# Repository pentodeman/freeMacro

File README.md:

# freeMacro rev. 1
A simple macro keypad that invokes key combinations, prints strings of text, and types special characters.

Special thanks to Arduino LLC for providing the Keyboard library that was used to create this project.
The library is available under:
https://github.com/arduino-libraries/Keyboard

## Features
* Typing strings, invoking macros, and typing special characters from the Unicode table
* 13 assignable banks with combinations of all three types of keypresses
* On the fly assignment of target operating system (Linux, Windows, macOS)
* Dependency free, plug and play
* Config generation handled by genConfig

## Default Firmware Behavior
* On power on, the board will flash each LED individually from the F key to the 0 key.
* Idle backlight should be steady without any flickering.
* On each keypress, only that key will be lit. Others will not.
* Holding down any key from 0 to C changes the current bank to that of they key held down.
* Pressing a key will invoke its macro (key combo, string, or Unicode).
* Holding down keys from D to F will change the target operating system:
  * D: Linux
  * E: Windows
  * F: macOS
* The default config initializes the bank to 9 and OS to Linux, if you prefer to use another combination, edit "banks.layout" and run genConfig (more instructions later).
* Bank and OS changes are indicated by the flash pattern:
  * fast: bank change
  * slow: OS change

## Modifying the config
* The firmware consists of two files:
  * freeMacro-firmware.ino: main firmware file that handles the logic
  * config.h: header file that houses all the functions called on keystrokes -> this is the config file
* Option 1: you can edit config.h directly if you want more control over your device (make sure to back up the default config in case of a rollback).
* Option 2: use genConfig and edit the soft config file (banks.layout).

## Arduino IDE is required for uploading the firmware (or Arduino CLI)
* Pro Micro boards are usually miniaturized Arduino Leonardos, selecting Arduino Leonardo in your board manager will likely work.
* In case of upload issues, make sure you selected the correct board and plugged it in. Communication issues can be caused by the serial port being busy or not having permissions to use the port (Googling the programmer error will usually solve the issue).

## Using genConfig
* This repo provides the source code for genConfig and a Linux binary.
* This program was only tested on Linux. Windows or macOS users may need to make changes to the source code, but this is unlikely. If you're using one of these systems, try compiling it first. For this you will need a C++ compiler. I used g++.
* Compiling genConfig from source:
  * This program does not use any third-party dependencies.
  * The only requirement for compilation is the C++ compiler itself; g++ is recommended.
  * To compile the program, follow these steps:
  
    ```git clone https://github.com/pentodeman/freeMacro```
    
    ```cd freeMacro```

    ```g++ genConfig.cpp -o genConfig```

    ```./genConfig --help```
  * It is not recommended to add genConfig to any binary directories (/bin, /sbin, /usr/bin, /usr/sbin, etc...) as the program outputs the file to its current working directory.
  * genConfig will look for the file called banks.layout in its current working directory and will output config.h
  * To generate a new config simply run:

    ```./genConfig``` for silent generation

    or

    ```./genConfig -v``` or ```./genConfig --verbose``` for verbose generation.
  * To use the new config, move the new config.h to the "freeMacro-firmware" directory and replace the old one (backing up your configs is recommended).
  * Once the new config.h is placed in the firmware directory, open the .ino file in Arduino IDE and upload it to your freeMacro board.
  * Instructions for modifying banks.layout are in the file itself and include a general template with all possible keywords.

## Assembly
* Required materials:
  * 1 PCB **make sure the PCB thickness is 1.6 mm** (Gerber files attached)
  * 16 3-pin full size mechanical switches of any kind (5-pin update coming soon in revision 2)
  * Electronic components listed in the BOM
  * 3D printed case (.stl files attached; feel free to design your own (.step file of the PCB can be generated in KiCad))
  * Low profile keycaps (currently full size keycaps have clearance issues with the enclosure)
* Tips for soldering the PCB:
  1. Start with the smallest and most repetitive components first (all passive and discrete components on the top plane).
  2. Solder the two multiplexer ICs.
  3. Clean the PCB thoroughly with isopropanol.
  4. Then solder the bottom LED current limiting resistors and clean the board again.
  5. Solder the Arduino Pro Micro FLUSH with the PCB. The case is designed to fit the microcontroller soldered directly to the PCB using included headers (see images folder).
    * feed the headers from the bottom of the freeMacro PCB and place the Arduino on top.
  6. After all electronic components are soldered, test the board by bridging switch pads with tweezers or any other conductor. Open any text editor and check if all characters are printed. Bank 9 of the default config is a good test.
  7. Once everything works, solder the switches. If you use the top shell with the plate, print the plate first and populate it with switches. It works as a good soldering guide. Make sure to test fit the entire device before soldering the switches.
  8. After soldering the switches, feed the LEDs throughand solder them. It's a good idea to just feed them and bend the leads for testing. Do it and plug in the board. If you see all LEDs shining (with some wiggling due to the lack of solder), the board works.
  9. Trim the leads, clean the board one last time, and assemble the case.
  10. Your board is ready, it's a good time to double check everything.

### Please note that this project is not a polished product. It's meant to be a fun project to tinker and experiment with. Working on it took me a total of one week worth of deisgn, coding, assembly, and testing. Please take imperfections with a grain of salt, as this is only a project delivered by a nerd to his fellow nerds. Happy tinkering!

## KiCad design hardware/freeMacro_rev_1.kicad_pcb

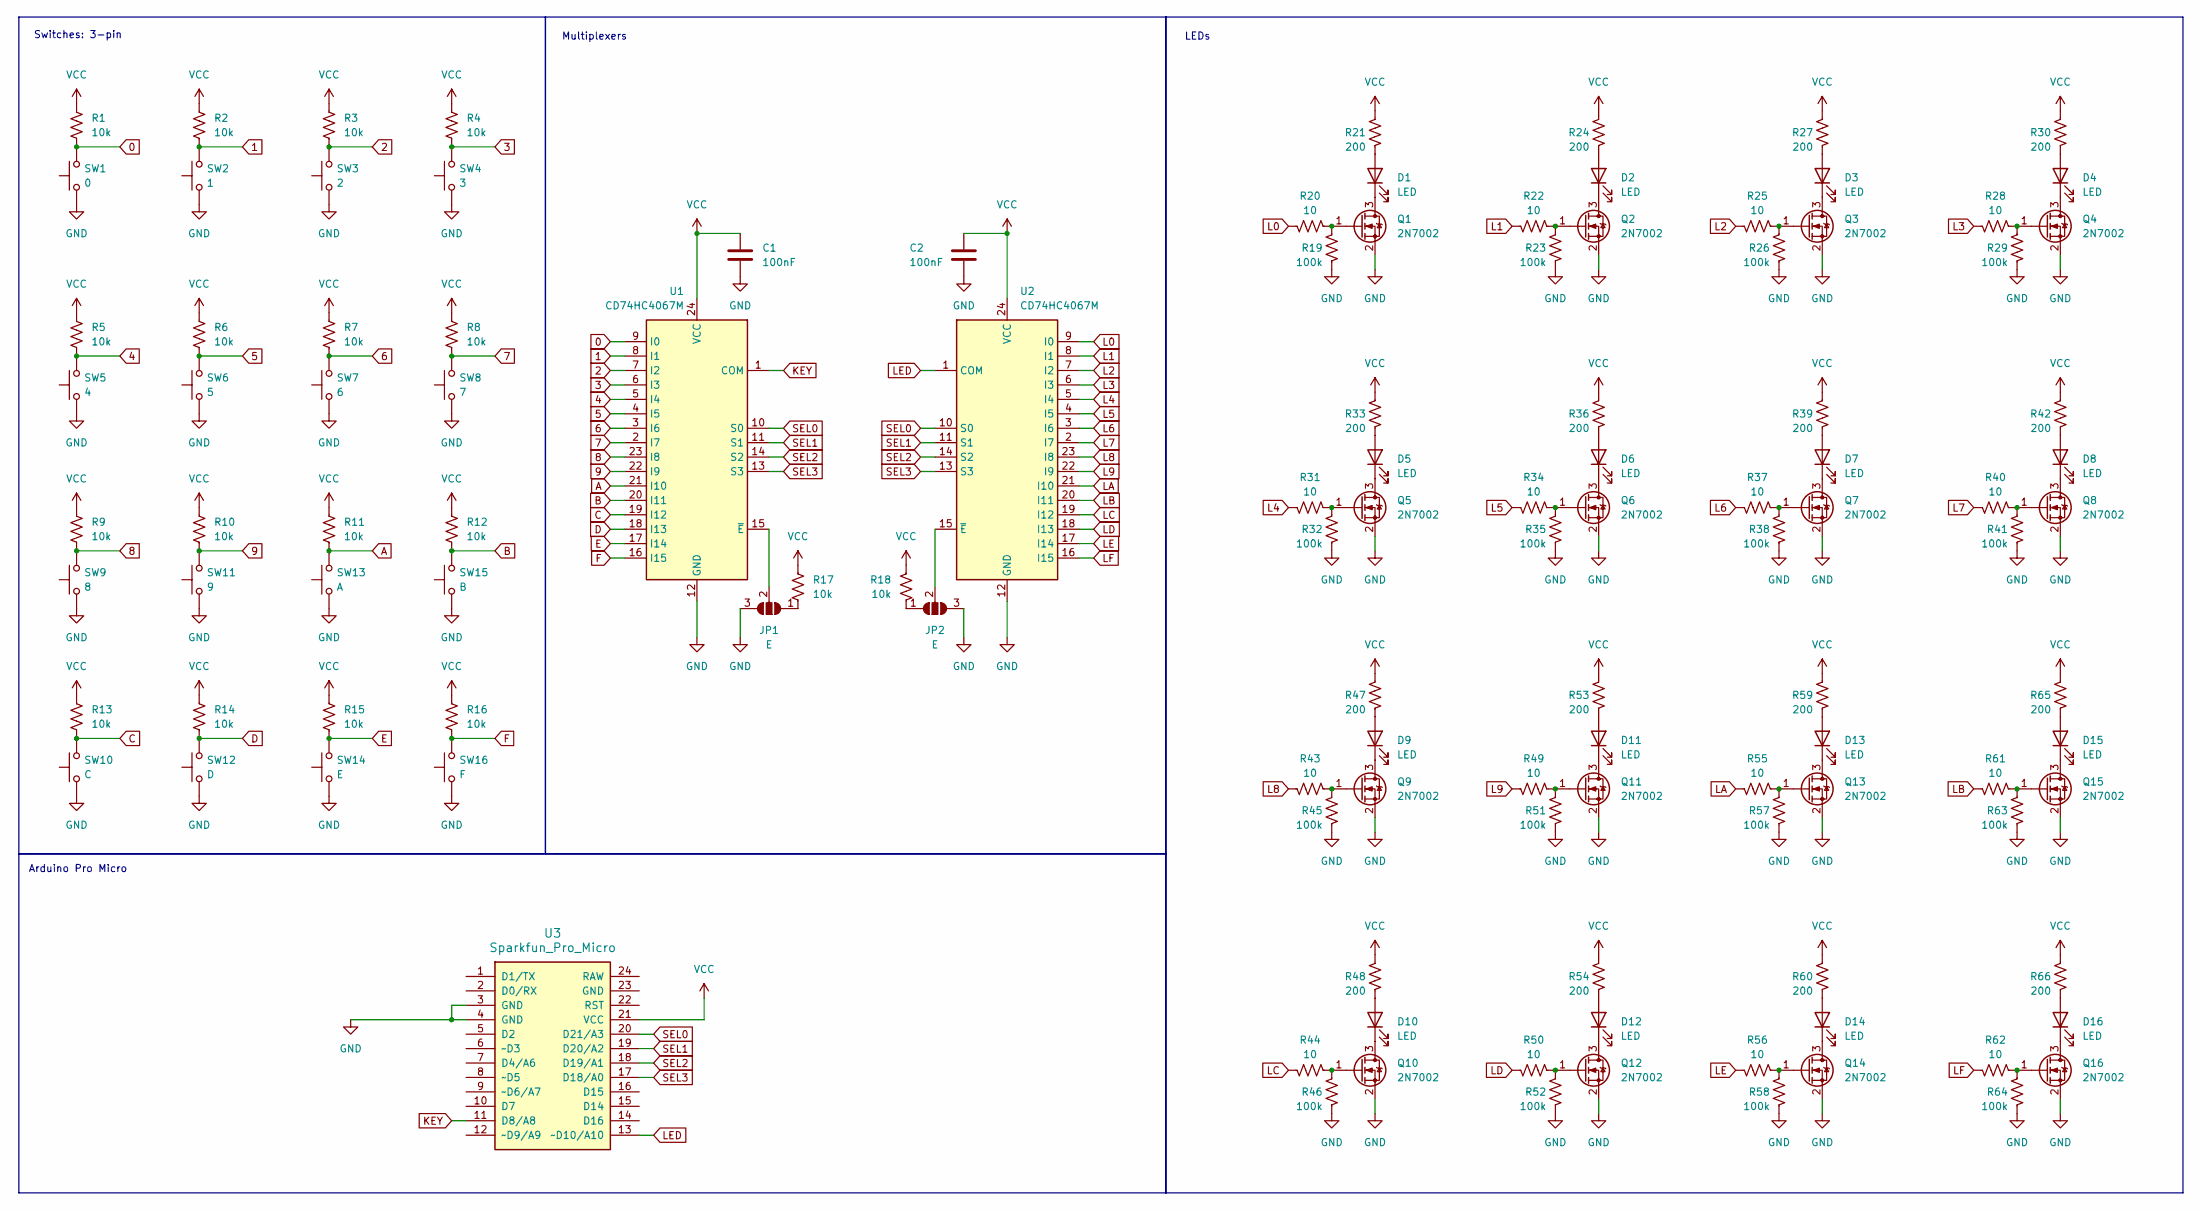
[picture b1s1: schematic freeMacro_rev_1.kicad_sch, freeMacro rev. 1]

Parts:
C1, C2: 100nF; C_0603_1608Metric_Pad1.08x0.95mm_HandSolder
D1, D2, D3, D4, D5, D6, D7, D8, D9, D10, D11, D12, D13, D14, D15, D16: LED; LED_D3.0mm
JP1, JP2: E; SolderJumper-3_P2.0mm_Open_TrianglePad1.0x1.5mm
Q1, Q2, Q3, Q4, Q5, Q6, Q7, Q8, Q9, Q10, Q11, Q12, Q13, Q14, Q15, Q16: 2N7002; SOT-23
R1, R2, R3, R4, R5, R6, R7, R8, R9, R10, R11, R12, R13, R14, R15, R16, R17, R18: 10k; R_0603_1608Metric_Pad0.98x0.95mm_HandSolder
R19, R23, R26, R29, R32, R35, R38, R41, R45, R46, R51, R52, R57, R58, R63, R64: 100k; R_0603_1608Metric_Pad0.98x0.95mm_HandSolder
R20, R22, R25, R28, R31, R34, R37, R40, R43, R44, R49, R50, R55, R56, R61, R62: 10; R_0603_1608Metric_Pad0.98x0.95mm_HandSolder
R21, R24, R27, R30, R33, R36, R39, R42, R47, R48, R53, R54, R59, R60, R65, R66: 200; R_0603_1608Metric_Pad0.98x0.95mm_HandSolder
SW1: 0; SW_Cherry_MX_1.00u_Plate
SW2: 1; SW_Cherry_MX_1.00u_Plate
SW3: 2; SW_Cherry_MX_1.00u_Plate
SW4: 3; SW_Cherry_MX_1.00u_Plate
SW5: 4; SW_Cherry_MX_1.00u_Plate
SW6: 5; SW_Cherry_MX_1.00u_Plate
SW7: 6; SW_Cherry_MX_1.00u_Plate
SW8: 7; SW_Cherry_MX_1.00u_Plate
SW9: 8; SW_Cherry_MX_1.00u_Plate
SW10: C; SW_Cherry_MX_1.00u_Plate
SW11: 9; SW_Cherry_MX_1.00u_Plate
SW12: D; SW_Cherry_MX_1.00u_Plate
SW13: A; SW_Cherry_MX_1.00u_Plate
SW14: E; SW_Cherry_MX_1.00u_Plate
SW15: B; SW_Cherry_MX_1.00u_Plate
SW16: F; SW_Cherry_MX_1.00u_Plate
U1, U2: CD74HC4067M; SOIC-24W_7.5x15.4mm_P1.27mm
U3: Sparkfun_Pro_Micro

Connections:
0: R1.2, SW1.2, U1.9 (I0)
1: R2.2, SW2.2, U1.8 (I1)
2: R3.2, SW3.2, U1.7 (I2)
3: R4.2, SW4.2, U1.6 (I3)
4: R5.2, SW5.2, U1.5 (I4)
5: R6.2, SW6.2, U1.4 (I5)
6: R7.2, SW7.2, U1.3 (I6)
7: R8.2, SW8.2, U1.2 (I7)
8: R9.2, SW9.2, U1.23 (I8)
9: R10.2, SW11.2, U1.22 (I9)
A: R11.2, SW13.2, U1.21 (I10)
B: R12.2, SW15.2, U1.20 (I11)
C: R13.2, SW10.2, U1.19 (I12)
D: R14.2, SW12.2, U1.18 (I13)
E: R15.2, SW14.2, U1.17 (I14)
F: R16.2, SW16.2, U1.16 (I15)
GND: C1.2, C2.2, JP1.3 (B), JP2.3 (B), Q1.2 (S), Q2.2 (S), Q3.2 (S), Q4.2 (S), Q5.2 (S), Q6.2 (S), Q7.2 (S), Q8.2 (S), Q9.2 (S), Q10.2 (S), Q11.2 (S), Q12.2 (S), Q13.2 (S), Q14.2 (S), Q15.2 (S), Q16.2 (S), R19.2, R23.2, R26.2, R29.2, R32.2, R35.2, R38.2, R41.2, R45.2, R46.2, R51.2, R52.2, R57.2, R58.2, R63.2, R64.2, SW1.1, SW2.1, SW3.1, SW4.1, SW5.1, SW6.1, SW7.1, SW8.1, SW9.1, SW10.1, SW11.1, SW12.1, SW13.1, SW14.1, SW15.1, SW16.1, U1.12 (GND), U2.12 (GND), U3.3 (GND), U3.4 (GND)
KEY: U1.1 (COM), U3.11 (D8/A8)
L0: R20.1, U2.9 (I0)
L1: R22.1, U2.8 (I1)
L2: R25.1, U2.7 (I2)
L3: R28.1, U2.6 (I3)
L4: R31.1, U2.5 (I4)
L5: R34.1, U2.4 (I5)
L6: R37.1, U2.3 (I6)
L7: R40.1, U2.2 (I7)
L8: R43.1, U2.23 (I8)
L9: R49.1, U2.22 (I9)
LA: R55.1, U2.21 (I10)
LB: R61.1, U2.20 (I11)
LC: R44.1, U2.19 (I12)
LD: R50.1, U2.18 (I13)
LE: R56.1, U2.17 (I14)
LED: U2.1 (COM), U3.13 (~D10/A10)
LF: R62.1, U2.16 (I15)
unnamed: D1.2 (A), R21.2
unnamed: D1.1 (K), Q1.3 (D)
unnamed: D2.2 (A), R24.2
unnamed: D2.1 (K), Q2.3 (D)
unnamed: D3.2 (A), R27.2
unnamed: D3.1 (K), Q3.3 (D)
unnamed: D4.2 (A), R30.2
unnamed: D4.1 (K), Q4.3 (D)
unnamed: D5.2 (A), R33.2
unnamed: D5.1 (K), Q5.3 (D)
unnamed: D6.2 (A), R36.2
unnamed: D6.1 (K), Q6.3 (D)
unnamed: D7.2 (A), R39.2
unnamed: D7.1 (K), Q7.3 (D)
unnamed: D8.2 (A), R42.2
unnamed: D8.1 (K), Q8.3 (D)
unnamed: D9.2 (A), R47.2
unnamed: D9.1 (K), Q9.3 (D)
unnamed: D10.2 (A), R48.2
unnamed: D10.1 (K), Q10.3 (D)
unnamed: D11.2 (A), R53.2
unnamed: D11.1 (K), Q11.3 (D)
unnamed: D12.2 (A), R54.2
unnamed: D12.1 (K), Q12.3 (D)
unnamed: D13.2 (A), R59.2
unnamed: D13.1 (K), Q13.3 (D)
unnamed: D14.2 (A), R60.2
unnamed: D14.1 (K), Q14.3 (D)
unnamed: D15.2 (A), R65.2
unnamed: D15.1 (K), Q15.3 (D)
unnamed: D16.2 (A), R66.2
unnamed: D16.1 (K), Q16.3 (D)
unnamed: JP1.1 (A), R17.2
unnamed: JP1.2 (C), U1.15 (~E)
unnamed: JP2.1 (A), R18.2
unnamed: JP2.2 (C), U2.15 (~E)
unnamed: Q1.1 (G), R19.1, R20.2
unnamed: Q2.1 (G), R22.2, R23.1
unnamed: Q3.1 (G), R25.2, R26.1
unnamed: Q4.1 (G), R28.2, R29.1
unnamed: Q5.1 (G), R31.2, R32.1
unnamed: Q6.1 (G), R34.2, R35.1
unnamed: Q7.1 (G), R37.2, R38.1
unnamed: Q8.1 (G), R40.2, R41.1
unnamed: Q9.1 (G), R43.2, R45.1
unnamed: Q10.1 (G), R44.2, R46.1
unnamed: Q11.1 (G), R49.2, R51.1
unnamed: Q12.1 (G), R50.2, R52.1
unnamed: Q13.1 (G), R55.2, R57.1
unnamed: Q14.1 (G), R56.2, R58.1
unnamed: Q15.1 (G), R61.2, R63.1
unnamed: Q16.1 (G), R62.2, R64.1
SEL0: U1.10 (S0), U2.10 (S0), U3.20 (D21/A3)
SEL1: U1.11 (S1), U2.11 (S1), U3.19 (D20/A2)
SEL2: U1.14 (S2), U2.14 (S2), U3.18 (D19/A1)
SEL3: U1.13 (S3), U2.13 (S3), U3.17 (D18/A0)
VCC: C1.1, C2.1, R1.1, R2.1, R3.1, R4.1, R5.1, R6.1, R7.1, R8.1, R9.1, R10.1, R11.1, R12.1, R13.1, R14.1, R15.1, R16.1, R17.1, R18.1, R21.1, R24.1, R27.1, R30.1, R33.1, R36.1, R39.1, R42.1, R47.1, R48.1, R53.1, R54.1, R59.1, R60.1, R65.1, R66.1, U1.24 (VCC), U2.24 (VCC), U3.21 (VCC)

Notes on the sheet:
Multiplexers
Switches: 3-pin
LEDs
Arduino Pro Micro

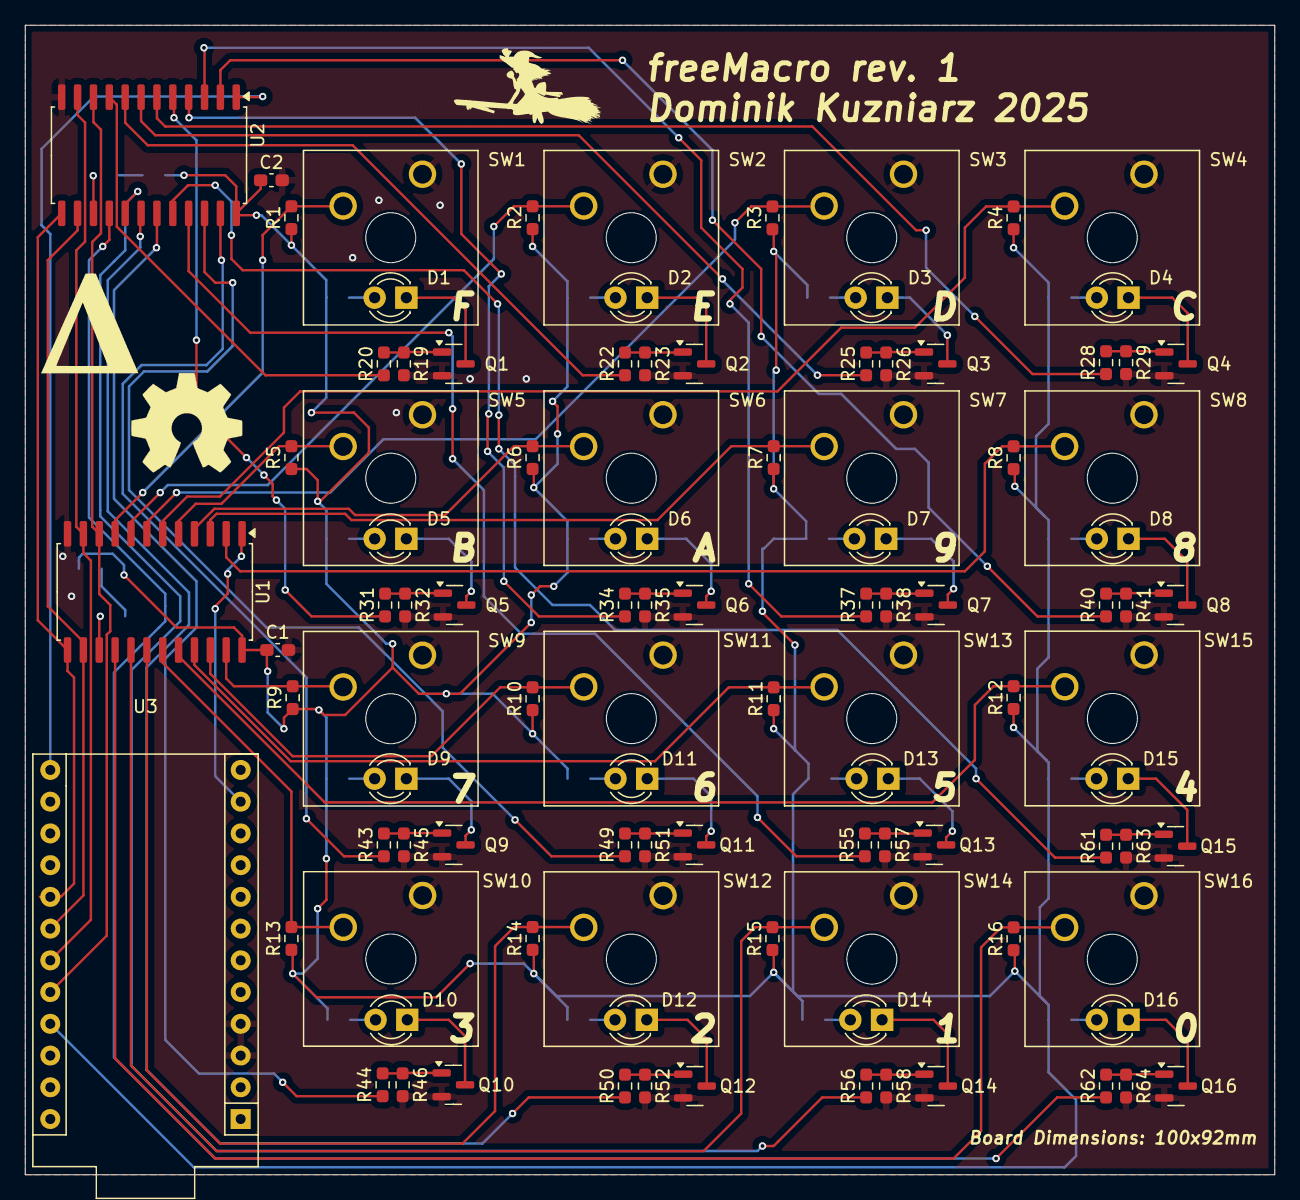
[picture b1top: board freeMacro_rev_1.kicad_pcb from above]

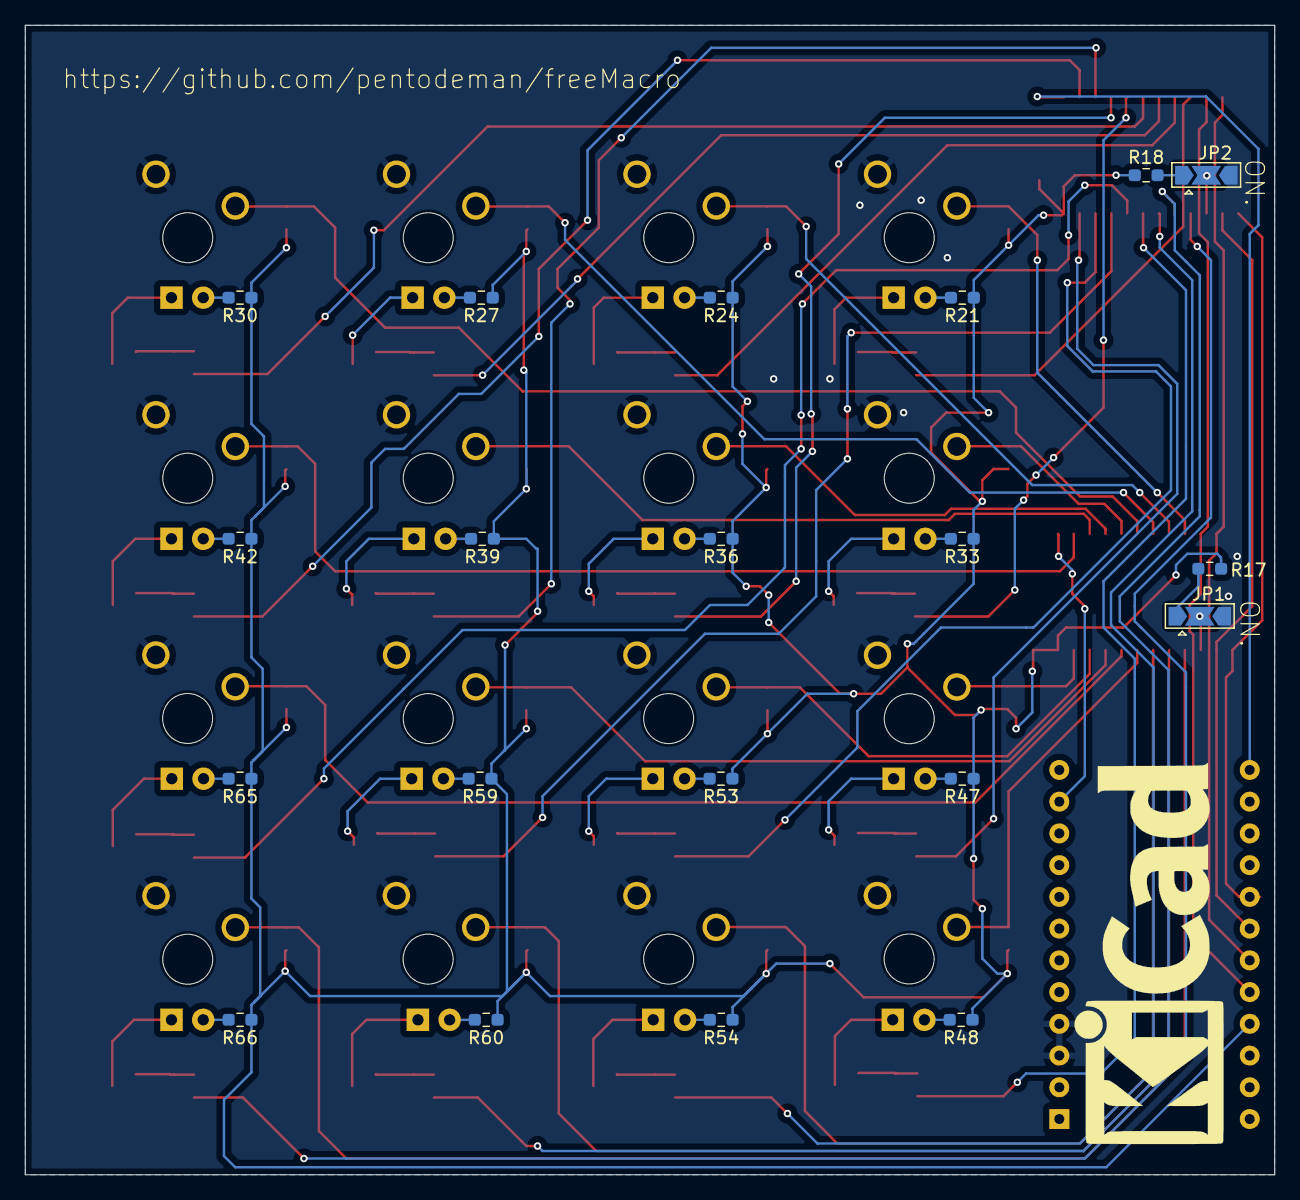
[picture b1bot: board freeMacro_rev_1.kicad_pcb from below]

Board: 2 copper layers, 100.0 x 92.0 mm, 121 parts (20 on the bottom side), 92 nets.

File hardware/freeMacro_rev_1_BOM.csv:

"Reference","Value","Datasheet","Footprint","Qty","DNP"
"C1,C2","100nF","~","Capacitor_SMD:C_0603_1608Metric_Pad1.08x0.95mm_HandSolder","2",""
"D1,D2,D3,D4,D5,D6,D7,D8,D9,D10,D11,D12,D13,D14,D15,D16","LED","~","LED_THT:LED_D3.0mm","16",""
"Q1,Q2,Q3,Q4,Q5,Q6,Q7,Q8,Q9,Q10,Q11,Q12,Q13,Q14,Q15,Q16","2N7002","https://www.onsemi.com/pub/Collateral/NDS7002A-D.PDF","Package_TO_SOT_SMD:SOT-23","16",""
"R1,R2,R3,R4,R5,R6,R7,R8,R9,R10,R11,R12,R13,R14,R15,R16,R17,R18","10k","~","Resistor_SMD:R_0603_1608Metric_Pad0.98x0.95mm_HandSolder","18",""
"R19,R23,R26,R29,R32,R35,R38,R41,R45,R46,R51,R52,R57,R58,R63,R64","100k","~","Resistor_SMD:R_0603_1608Metric_Pad0.98x0.95mm_HandSolder","16",""
"R20,R22,R25,R28,R31,R34,R37,R40,R43,R44,R49,R50,R55,R56,R61,R62","10","~","Resistor_SMD:R_0603_1608Metric_Pad0.98x0.95mm_HandSolder","16",""
"R21,R24,R27,R30,R33,R36,R39,R42,R47,R48,R53,R54,R59,R60,R65,R66","200","~","Resistor_SMD:R_0603_1608Metric_Pad0.98x0.95mm_HandSolder","16",""
"U1,U2","CD74HC4067M","http://www.ti.com/lit/ds/symlink/cd74hc4067.pdf","Package_SO:SOIC-24W_7.5x15.4mm_P1.27mm","2",""

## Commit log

2025-03-25 Committed source files
2025-03-25 Added the "hardware" folder
2025-03-25 Added default enclosure files
